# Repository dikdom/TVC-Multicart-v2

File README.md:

# TVC-Multicart-v2
Copyright (C) 2017-2019 by Sandor Vass <vass.sanyi@gmail.com>  
All rights reserved.

# About #
The multicart is a flash storage device for the Videoton TV Computer, 
inserted to the left side expansion slot (program-module).
This repository contains all the related source files to build one 
from scratch.

# Structure #

*  doc

   Contains descriptions and help how to solder and program a module.
   Also a short explanation the structure of the repo, Hungarian.

*  hardware

   Eagle source files and gerber files of the PCB.

*  software

   *  firmware

      The multicart firmware source and binary, that drives the whole stuff. The
      binary is needed to build a complete multicart.

   *  rom-builder

      The source of the Lazarus program (Multiplatform, free pascal IDE), that 
      aids the building of the ROM images to be written to the onboaed EEPROM chips.

   *  tvcpla

      The source of the pla binary generator, and the generated binary also.

# License #

The firmware itself is distributed under the following conditions:

    Redistribution and use in source and binary forms, with or without
    modification, are permitted provided that the following conditions
    are met:
    1. Redistributions of source code must retain the above copyright
       notice, this list of conditions and the following disclaimer.
    2. Redistributions in binary form must reproduce the above copyright
       notice, this list of conditions and the following disclaimer in the
       documentation and/or other materials provided with the distribution.

    THIS SOFTWARE IS PROVIDED BY THE REGENTS AND CONTRIBUTORS ``AS IS'' AND
    ANY EXPRESS OR IMPLIED WARRANTIES, INCLUDING, BUT NOT LIMITED TO, THE
    IMPLIED WARRANTIES OF MERCHANTABILITY AND FITNESS FOR A PARTICULAR PURPOSE
    ARE DISCLAIMED.  IN NO EVENT SHALL THE REGENTS OR CONTRIBUTORS BE LIABLE
    FOR ANY DIRECT, INDIRECT, INCIDENTAL, SPECIAL, EXEMPLARY, OR CONSEQUENTIAL
    DAMAGES (INCLUDING, BUT NOT LIMITED TO, PROCUREMENT OF SUBSTITUTE GOODS
    OR SERVICES; LOSS OF USE, DATA, OR PROFITS; OR BUSINESS INTERRUPTION)
    HOWEVER CAUSED AND ON ANY THEORY OF LIABILITY, WHETHER IN CONTRACT, STRICT
    LIABILITY, OR TORT (INCLUDING NEGLIGENCE OR OTHERWISE) ARISING IN ANY WAY
    OUT OF THE USE OF THIS SOFTWARE, EVEN IF ADVISED OF THE POSSIBILITY OF
    SUCH DAMAGE.

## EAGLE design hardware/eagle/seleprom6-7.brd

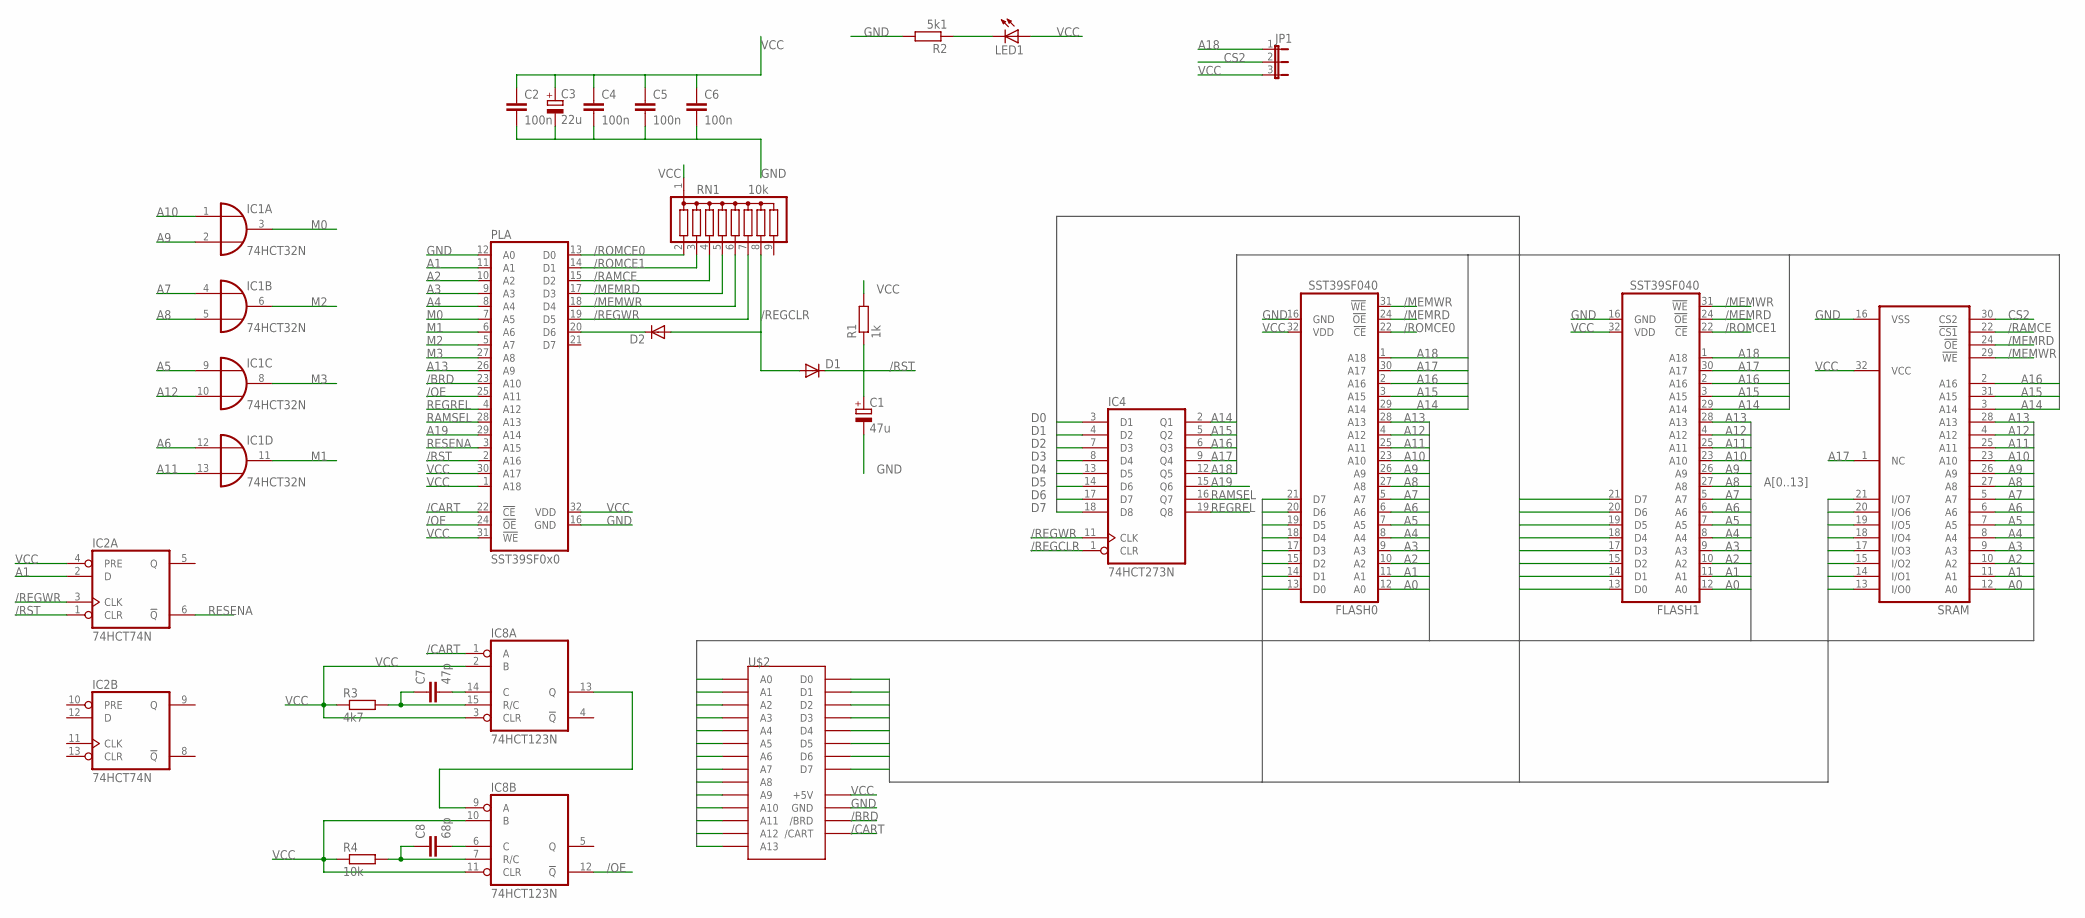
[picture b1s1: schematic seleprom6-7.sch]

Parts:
C1: 47u; E2,5-5
C2, C4, C5, C6: 100n; C025-025X050
C3: 22u; E2-4
C7: 47p; C025-025X050
C8: 68p; C025-025X050
D1, D2: DIODE-D-5; D-5
FLASH0, FLASH1: SST39SF040; PLCC-SR32
IC1: 74HCT32N; DIL14
IC2: 74HCT74N; DIL14
IC4: 74HCT273N; DIL20
IC8: 74HCT123N; DIL16
JP1: JP2E; JP2
LED1: LED3MM
PLA: SST39SF0x0; PLCC-SR32
R1: 1k; 0204/7
R2: 5k1; 0204/7
R3: 4k7; 0204/7
R4: 10k; 0204/7
RN1: 10k; SIL9
SRAM: 628128P; DIL32
U$2: TVC-CARD+; TVC-CART-CARD

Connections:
/BRD: PLA.23 (A10), U$2.BTM24 (/BRD)
/CART: IC8.1 (A), PLA.22 (!CE), U$2.BTM23 (/CART)
/MEMRD: FLASH0.24 (!OE), FLASH1.24 (!OE), PLA.17 (D3), RN1.5, SRAM.24 (!OE)
/MEMWR: FLASH0.31 (!WE), FLASH1.31 (!WE), PLA.18 (D4), RN1.6, SRAM.29 (!WE)
/OE: IC8.12 (!Q), PLA.24 (!OE), PLA.25 (A11)
/RAMCE: PLA.15 (D2), RN1.4, SRAM.22 (!CS1)
/REGCLR: D1.A, D2.A, IC4.1 (CLR), RN1.8
/REGWR: IC2.3 (CLK), IC4.11 (CLK), PLA.19 (D5), RN1.7
/ROMCE0: FLASH0.22 (!CE), PLA.13 (D0), RN1.2
/ROMCE1: FLASH1.22 (!CE), PLA.14 (D1), RN1.3
/RST: C1.+, D1.C, IC2.1 (CLR), PLA.2 (A16), R1.1
A0: FLASH0.12 (A0), FLASH1.12 (A0), SRAM.12 (A0), U$2.TOP25 (A0)
A1: FLASH0.11 (A1), FLASH1.11 (A1), IC2.2 (D), PLA.11 (A1), SRAM.11 (A1), U$2.TOP2 (A1)
A2: FLASH0.10 (A2), FLASH1.10 (A2), PLA.10 (A2), SRAM.10 (A2), U$2.TOP24 (A2)
A3: FLASH0.9 (A3), FLASH1.9 (A3), PLA.9 (A3), SRAM.9 (A3), U$2.TOP1 (A3)
A4: FLASH0.8 (A4), FLASH1.8 (A4), PLA.8 (A4), SRAM.8 (A4), U$2.TOP21 (A4)
A5: FLASH0.7 (A5), FLASH1.7 (A5), IC1.9 (I0), SRAM.7 (A5), U$2.TOP14 (A5)
A6: FLASH0.6 (A6), FLASH1.6 (A6), IC1.12 (I0), SRAM.6 (A6), U$2.TOP18 (A6)
A7: FLASH0.5 (A7), FLASH1.5 (A7), IC1.4 (I0), SRAM.5 (A7), U$2.TOP17 (A7)
A8: FLASH0.27 (A8), FLASH1.27 (A8), IC1.5 (I1), SRAM.27 (A8), U$2.TOP15 (A8)
A9: FLASH0.26 (A9), FLASH1.26 (A9), IC1.2 (I1), SRAM.26 (A9), U$2.TOP19 (A9)
A10: FLASH0.23 (A10), FLASH1.23 (A10), IC1.1 (I0), SRAM.23 (A10), U$2.TOP22 (A10)
A11: FLASH0.25 (A11), FLASH1.25 (A11), IC1.13 (I1), SRAM.25 (A11), U$2.TOP20 (A11)
A12: FLASH0.4 (A12), FLASH1.4 (A12), IC1.10 (I1), SRAM.4 (A12), U$2.TOP16 (A12)
A13: FLASH0.28 (A13), FLASH1.28 (A13), PLA.26 (A9), SRAM.28 (A13), U$2.TOP23 (A13)
A14: FLASH0.29 (A14), FLASH1.29 (A14), IC4.2 (Q1), SRAM.3 (A14)
A15: FLASH0.3 (A15), FLASH1.3 (A15), IC4.5 (Q2), SRAM.31 (A15)
A16: FLASH0.2 (A16), FLASH1.2 (A16), IC4.6 (Q3), SRAM.2 (A16)
A17: FLASH0.30 (A17), FLASH1.30 (A17), IC4.9 (Q4), SRAM.1 (NC)
A18: FLASH0.1 (A18), FLASH1.1 (A18), IC4.12 (Q5), JP1.1
A19: IC4.15 (Q6), PLA.29 (A14)
CS2: JP1.2, SRAM.30 (CS2)
D0: FLASH0.13 (D0), FLASH1.13 (D0), IC4.3 (D1), SRAM.13 (I/O0), U$2.TOP4 (D0)
D1: FLASH0.14 (D1), FLASH1.14 (D1), IC4.4 (D2), SRAM.14 (I/O1), U$2.TOP5 (D1)
D2: FLASH0.15 (D2), FLASH1.15 (D2), IC4.7 (D3), SRAM.15 (I/O2), U$2.TOP6 (D2)
D3: FLASH0.17 (D3), FLASH1.17 (D3), IC4.8 (D4), SRAM.17 (I/O3), U$2.TOP7 (D3)
D4: FLASH0.18 (D4), FLASH1.18 (D4), IC4.13 (D5), SRAM.18 (I/O4), U$2.TOP8 (D4)
D5: FLASH0.19 (D5), FLASH1.19 (D5), IC4.14 (D6), SRAM.19 (I/O5), U$2.TOP9 (D5)
D6: FLASH0.20 (D6), FLASH1.20 (D6), IC4.17 (D7), SRAM.20 (I/O6), U$2.TOP10 (D6)
D7: FLASH0.21 (D7), FLASH1.21 (D7), IC4.18 (D8), SRAM.21 (I/O7), U$2.TOP3 (D7)
GND: C1.-, C2.2, C3.-, C4.2, C5.2, C6.2, FLASH0.16 (GND), FLASH1.16 (GND), IC1.7 (GND), IC2.7 (GND), IC4.10 (GND), IC8.8 (GND), PLA.12 (A0), PLA.16 (GND), R2.2, SRAM.16 (VSS), U$2.BTM1 (GND), U$2.BTM2 (GND), U$2.BTM3 (GND), U$2.BTM4 (GND), U$2.BTM5 (GND), U$2.BTM6 (GND), U$2.BTM7 (GND), U$2.BTM8 (GND)
M0: IC1.3 (O), PLA.7 (A5)
M1: IC1.11 (O), PLA.6 (A6)
M2: IC1.6 (O), PLA.5 (A7)
M3: IC1.8 (O), PLA.27 (A8)
unnamed: D2.C, PLA.20 (D6)
unnamed: LED1.K (C), R2.1
unnamed: IC8.9 (A), IC8.13 (Q)
unnamed: C7.2, IC8.14 (C)
unnamed: C8.2, IC8.6 (C)
unnamed: C8.1, IC8.7 (R/C), R4.2
unnamed: C7.1, IC8.15 (R/C), R3.2
RAMSEL: IC4.16 (Q7), PLA.28 (A13)
REGREL: IC4.19 (Q8), PLA.4 (A12)
RESENA: IC2.6 (!Q), PLA.3 (A15)
VCC: C2.1, C3.+, C4.1, C5.1, C6.1, FLASH0.32 (VDD), FLASH1.32 (VDD), IC1.14 (VCC), IC2.4 (PRE), IC2.14 (VCC), IC4.20 (VCC), IC8.2 (B), IC8.3 (CLR), IC8.10 (B), IC8.11 (CLR), IC8.16 (VCC), JP1.3, LED1.A, PLA.1 (A18), PLA.30 (A17), PLA.31 (!WE), PLA.32 (VDD), R1.2, R3.1, R4.1, RN1.1, SRAM.32 (VCC), U$2.BTM10 (+5V), U$2.BTM11 (+5V), U$2.BTM12 (+5V), U$2.BTM13 (+5V), U$2.BTM14 (+5V), U$2.BTM15 (+5V), U$2.BTM16 (+5V), U$2.BTM17 (+5V)

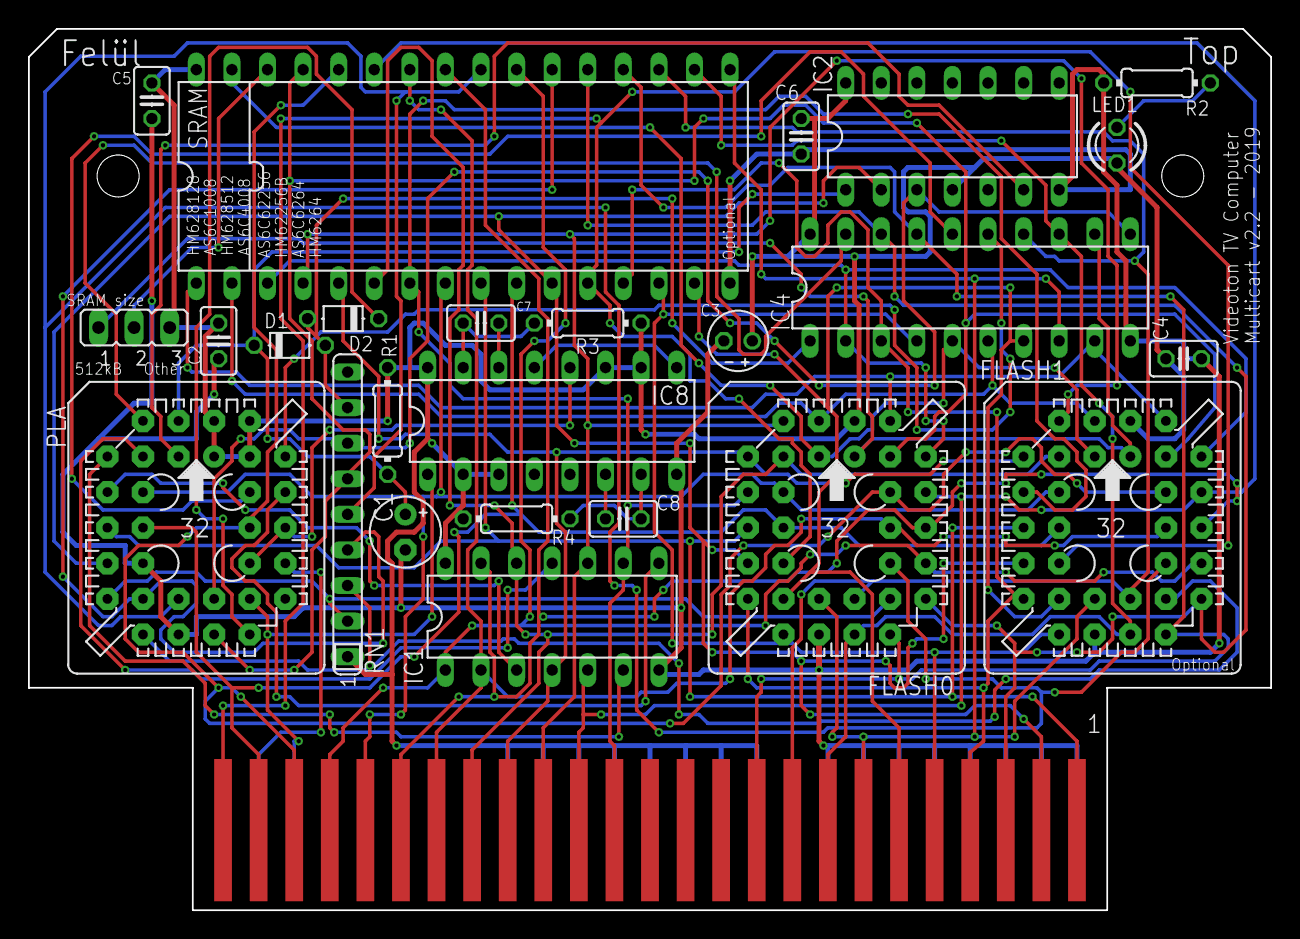
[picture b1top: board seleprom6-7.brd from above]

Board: 2 copper layers, 88.7 x 62.9 mm, 26 parts (0 on the bottom side), 56 nets.

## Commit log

2019-04-02 Readme extended a bit
2019-09-22 Initial commit message. This commit contains all the files needed for building a TVC Multicart card from scratch.
2019-09-22 firmware binary added, readme.txt modified
2019-09-23 License info added, firmware included
2019-09-23 Directory structure explained
2020-01-15 pdf files added
    Schematics, layout and print files (for DIY warriors) in PDF format.
